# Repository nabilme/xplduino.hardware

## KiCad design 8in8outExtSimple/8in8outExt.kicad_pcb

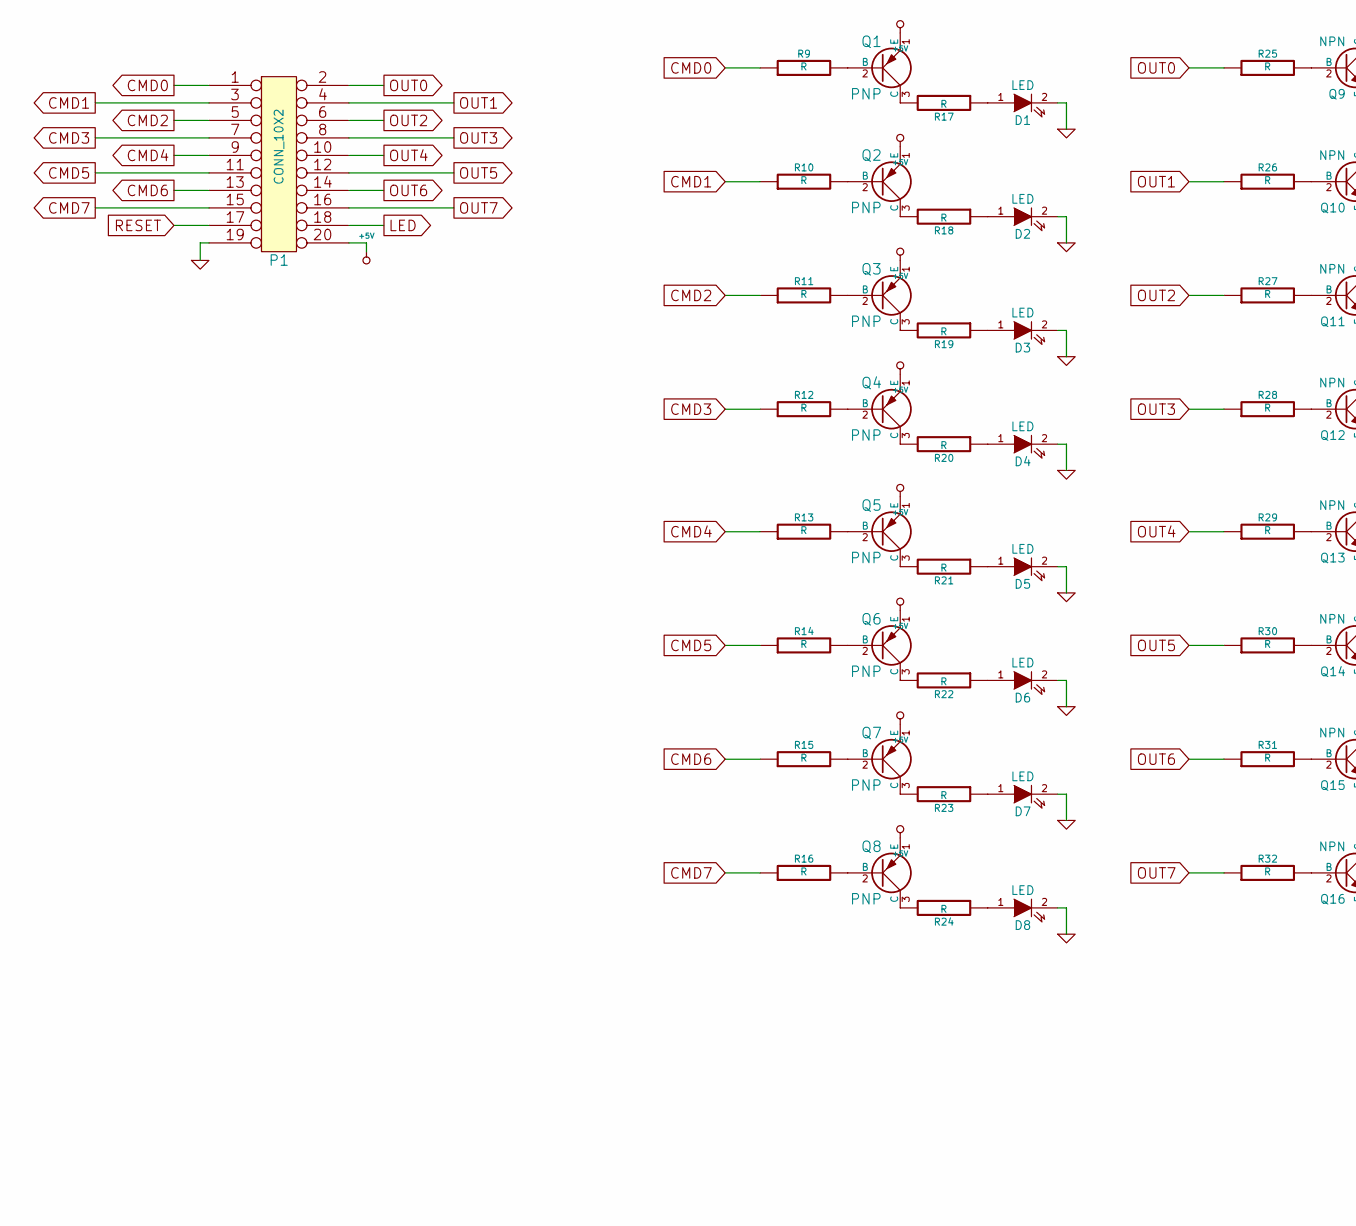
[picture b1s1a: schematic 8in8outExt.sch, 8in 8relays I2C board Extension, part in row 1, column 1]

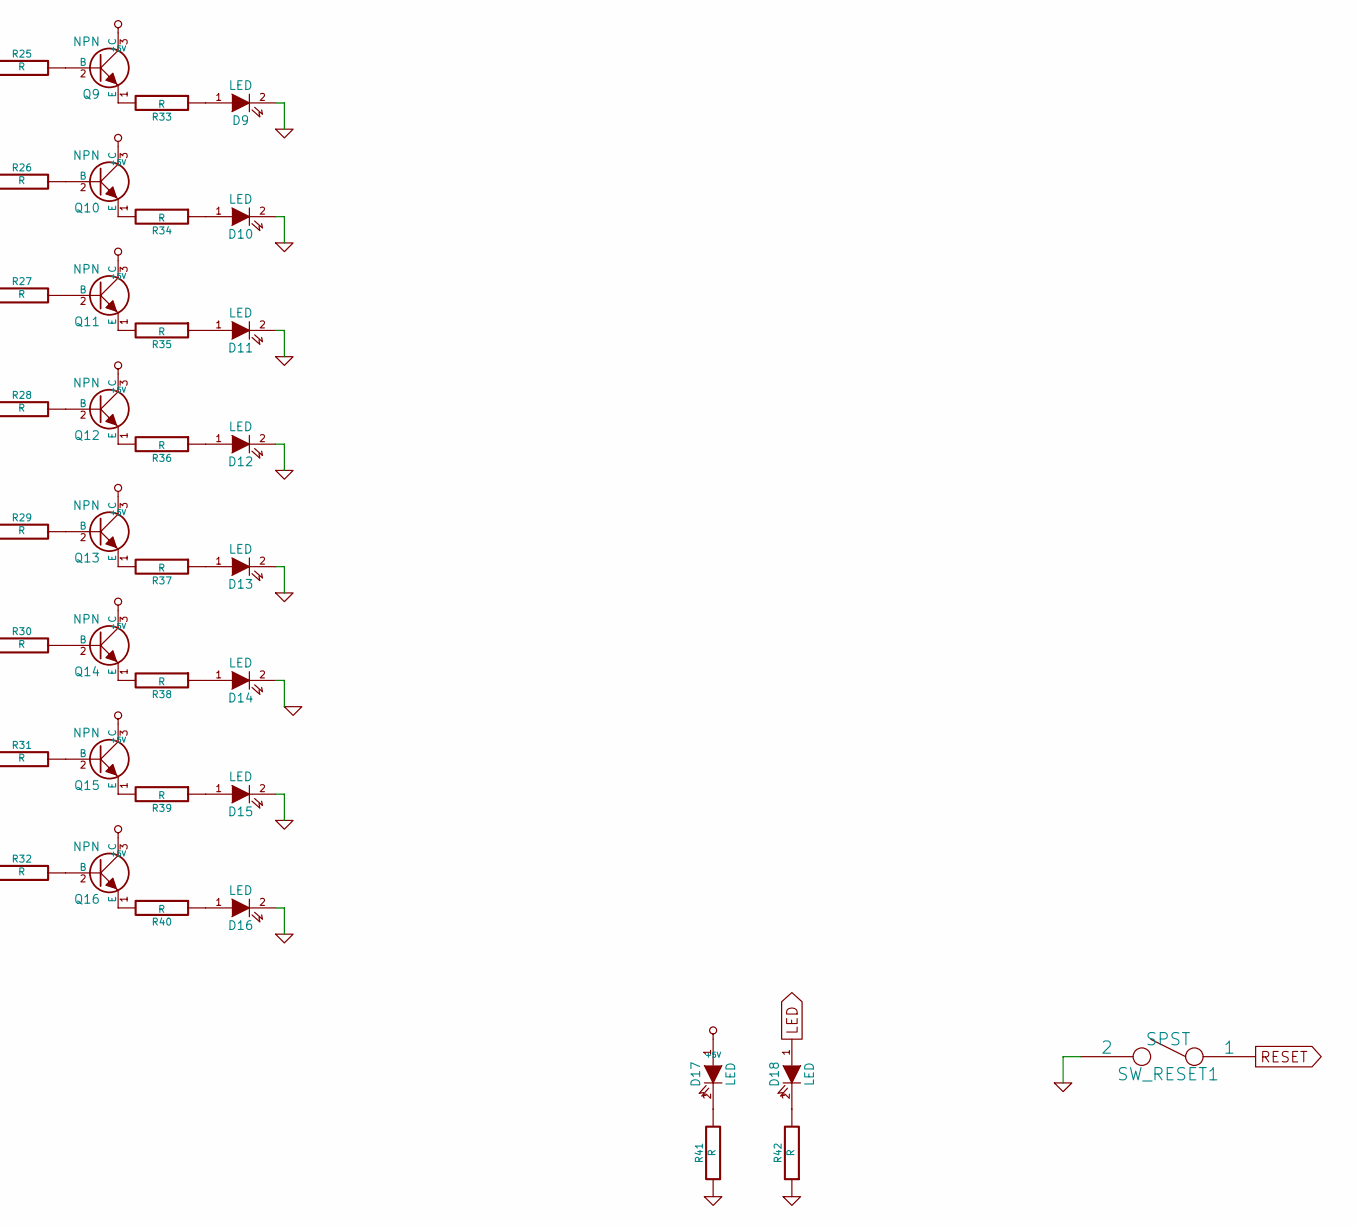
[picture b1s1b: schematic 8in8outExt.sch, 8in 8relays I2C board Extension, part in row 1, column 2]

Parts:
D1, D2, D3, D4, D5, D6, D7, D8, D9, D10, D11, D12, D13, D14, D15, D16, D17, D18: LED
P1: CONN_10X2
Q1, Q2, Q3, Q4, Q5, Q6, Q7, Q8: PNP
Q9, Q10, Q11, Q12, Q13, Q14, Q15, Q16: NPN
R9, R10, R11, R12, R13, R14, R15, R16, R25, R26, R27, R28, R29, R30, R31, R32: R
R17, R18, R19, R20, R21, R22, R23, R24, R33, R34, R35, R36, R37, R38, R39, R40, R41, R42: R
SW_RESET1: SPST

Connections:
+5V: D17.1 (A), P1.20, Q1.1 (E), Q2.1 (E), Q3.1 (E), Q4.1 (E), Q5.1 (E), Q6.1 (E), Q7.1 (E), Q8.1 (E), Q9.3 (C), Q10.3 (C), Q11.3 (C), Q12.3 (C), Q13.3 (C), Q14.3 (C), Q15.3 (C), Q16.3 (C); also elsewhere on the board
CMD0: P1.1, R9.1
CMD1: P1.3, R10.1
CMD2: P1.5, R11.1
CMD3: P1.7, R12.1
CMD4: P1.9, R13.1
CMD5: P1.11, R14.1
CMD6: P1.13, R15.1
CMD7: P1.15, R16.1
unnamed: Q9.2 (B), R25.2
unnamed: Q10.1 (E), R34.2
unnamed: D10.1 (A), R34.1
unnamed: Q9.1 (E), R33.2
unnamed: D9.1 (A), R33.1
unnamed: D11.1 (A), R35.1
unnamed: Q11.2 (B), R27.2
unnamed: Q11.1 (E), R35.2
unnamed: Q10.2 (B), R26.2
unnamed: Q7.3 (C), R23.2
unnamed: D7.1 (A), R23.1
unnamed: Q6.2 (B), R14.2
unnamed: Q6.3 (C), R22.2
unnamed: D6.1 (A), R22.1
unnamed: D8.1 (A), R24.1
unnamed: Q8.2 (B), R16.2
unnamed: Q8.3 (C), R24.2
unnamed: Q7.2 (B), R15.2
unnamed: D16.1 (A), R40.1
unnamed: Q15.2 (B), R31.2
unnamed: Q15.1 (E), R39.2
unnamed: D15.1 (A), R39.1
unnamed: Q14.2 (B), R30.2
unnamed: Q14.1 (E), R38.2
unnamed: Q16.1 (E), R40.2
unnamed: Q16.2 (B), R32.2
unnamed: D13.1 (A), R37.1
unnamed: Q12.2 (B), R28.2
unnamed: Q12.1 (E), R36.2
unnamed: Q13.1 (E), R37.2
unnamed: D12.1 (A), R36.1
unnamed: D14.1 (A), R38.1
unnamed: Q13.2 (B), R29.2
unnamed: D17.2 (K), R41.2
unnamed: Q1.3 (C), R17.2
unnamed: D1.1 (A), R17.1
unnamed: Q4.3 (C), R20.2
unnamed: D4.1 (A), R20.1
unnamed: Q4.2 (B), R12.2
unnamed: Q3.2 (B), R11.2
unnamed: Q3.3 (C), R19.2
unnamed: Q5.2 (B), R13.2
unnamed: Q5.3 (C), R21.2
unnamed: D3.1 (A), R19.1
unnamed: D5.1 (A), R21.1
unnamed: Q1.2 (B), R9.2
unnamed: Q2.2 (B), R10.2
unnamed: Q2.3 (C), R18.2
unnamed: D2.1 (A), R18.1
OUT0: P1.2, R25.1
OUT1: P1.4, R26.1
OUT2: P1.6, R27.1
OUT3: P1.8, R28.1
OUT4: P1.10, R29.1
OUT5: P1.12, R30.1
OUT6: P1.14, R31.1
OUT7: P1.16, R32.1
RESET: P1.17, SW_RESET1.1

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
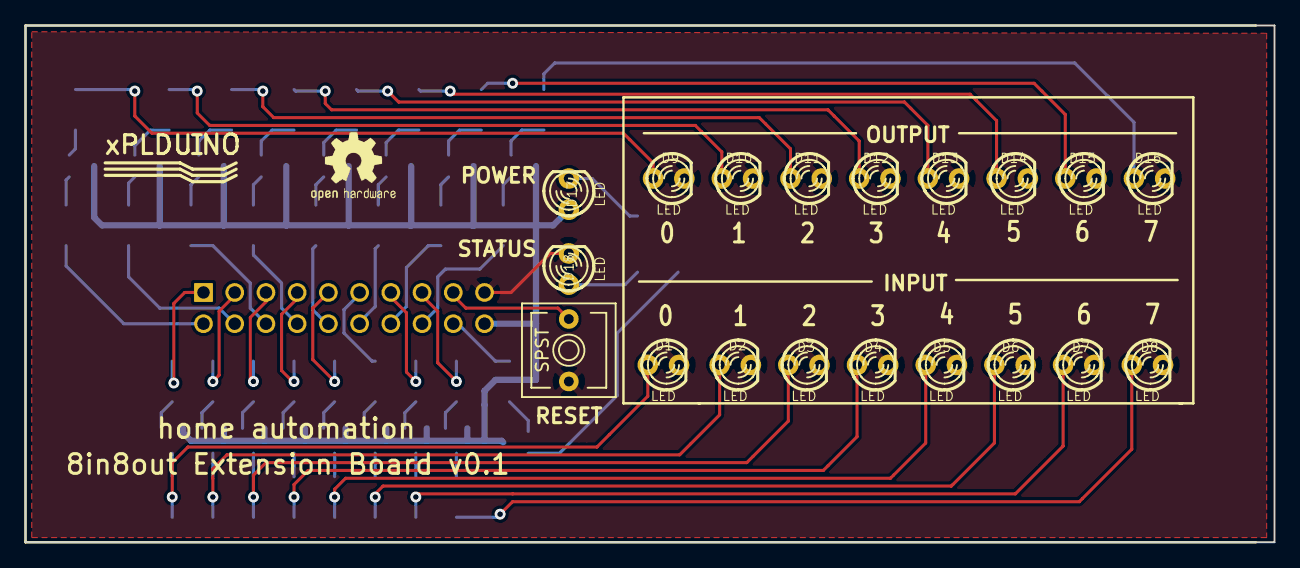
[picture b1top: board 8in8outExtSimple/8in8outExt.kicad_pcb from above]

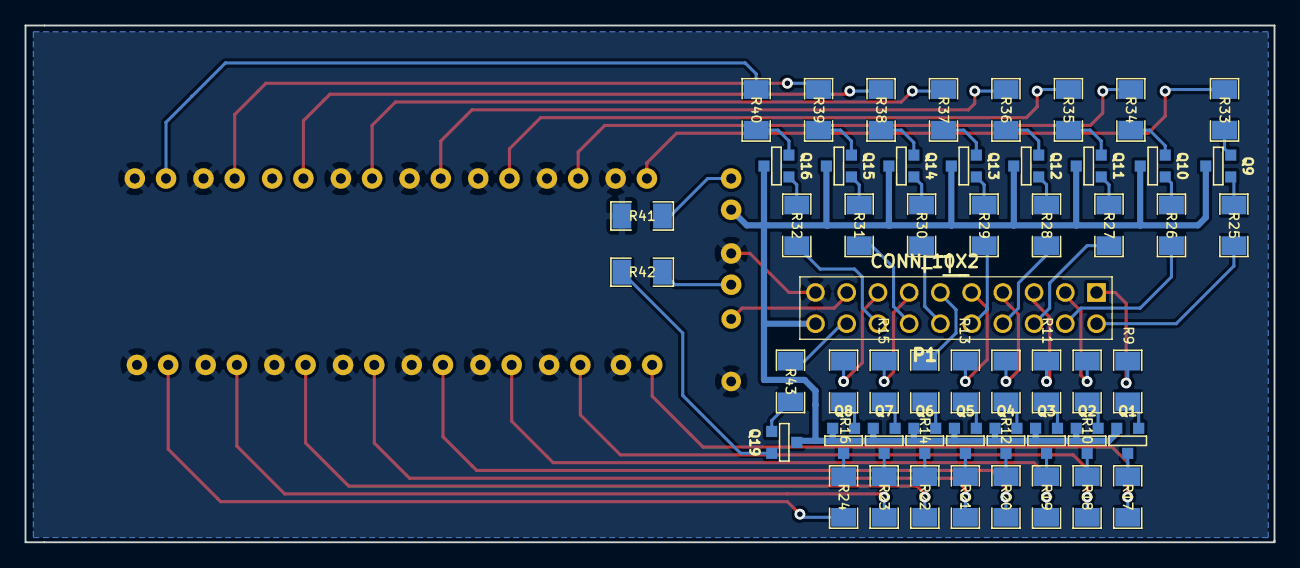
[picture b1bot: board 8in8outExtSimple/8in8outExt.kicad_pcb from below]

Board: 2 copper layers, 101.6 x 42.0 mm, 73 parts (53 on the bottom side), 72 nets.

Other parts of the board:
Q19: NPN; SOT23EBC
R43: R; SM1206
logo_xplduino: VAL**; logo_xplduino

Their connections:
+5V: Q19.3; also elsewhere on the board
unnamed: Q19.2, R43.2

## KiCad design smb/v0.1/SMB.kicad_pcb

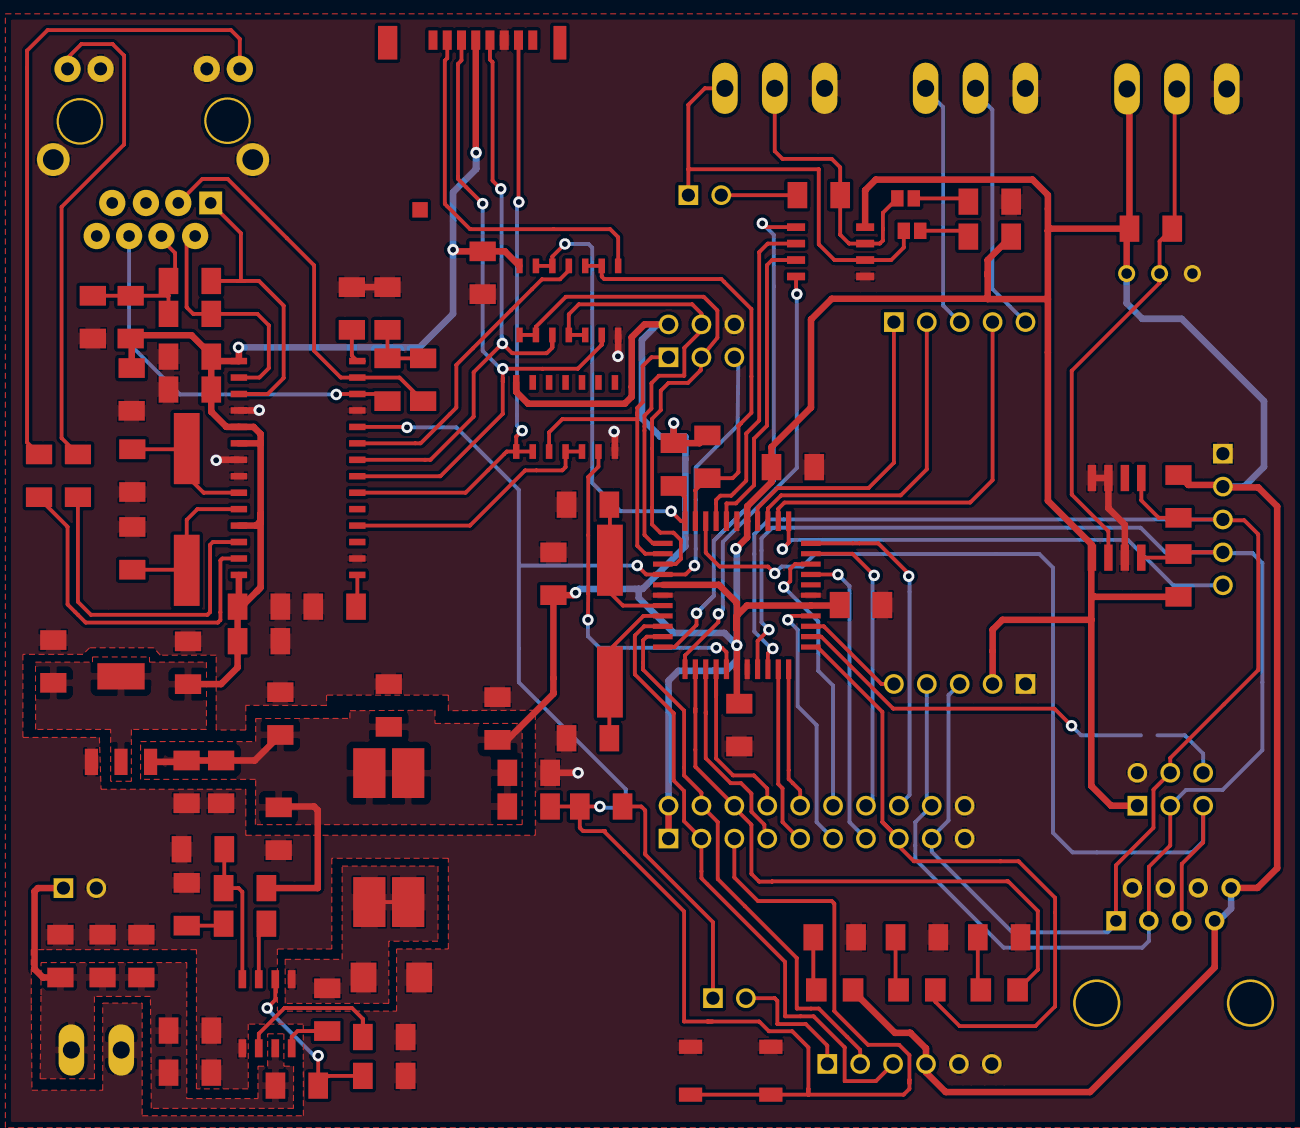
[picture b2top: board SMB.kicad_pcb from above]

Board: 2 copper layers, 98 parts (0 on the bottom side), 80 nets.

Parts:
C101, C102, C103, C104, C107, C203, C204, C205, C206, C207, C215: 0.1uF; SM1206
C105, C106, C201, C202: 18pF; SM1206
C208, C213: 10uF; SM1206POL
C209, C210, C212, C214, C309: 100nF; SM1206
C211: 10nF; SM1206
C301, C303, C304, C310, C311: 1uF; SM1206
C302: 150pF; SM1206POL
C305, C306, C307, C308, C312: 4.7uF; SM1206
D101, D102, D103: LED; LED-1206
D301: B280-13-F; B290-13-F
GS1, GS2, GS3: GS2
IC1: MAX485; SO8E
IC2: DS2482-100S; 1wire-SO08
IC101: ATMEGA1284-A; TQFP44
J101: RJ45; RJ45_BASIC
J102: RTS_RESET; PIN_ARRAY_2X1
J103: ICSP; pin_array_3x2
J104: SERIAL_REV; PIN_ARRAY-6X1
J202: USD_CONN; DM3CS-SF
J401: HR911105_RJ45
L201: 4.7uH; SM1206
L301: SRF1260-150M
P1: CONN_2; PIN_ARRAY_2X1
P2: CONN_3; 1wire-TO92-
P101: I2C_CONN; HE10-6
P102: CONN_10X2; pin_array_10x2
P103, P105, P108: CONN_5; PIN_ARRAY_5x1
P107, P110, P112: CONN_3; MOL_CONN_3_MINI
P109: CONN_3; PIN_ARRAY_2X1
P301: CONN_2; MOL_CONN_2_MINI
R1, R5, R102: 3.3kR; SM1206
R2, R3, R4, R105, R106: R; SM1206
R101, R103, R104: 10k; SM1206
R200: 4.7k; SM1206
R201: 2k32; SM1206
R203, R204, R205, R206: 50; SM1206
R301: 17.4k; SM1206
R302: 100k; SM1206
R303: 200k; SM1206
R304: 158k; SM1206
R305: 40.2k; SM1206
R306: 210k; SM1206
R401, R402: 270R; SM1206
SW101: SKQGAKE010
U201: ENC28J60; SO28
U202: LM1117IMP-3.3; SOT223
U301, U303: 74HC08; SO14E
U302: MP2562DS; SO8E
X101: 20MHz; Q_49U3HMS
X201: 25MHz; Q_49U3HMS
logo_xplduino: VAL**; logo_xplduino

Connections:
3.3V: C203.2, C204.2, C205.1, C206.1, C207.1, C213.1, C214.1, C215.2, J202.4, L201.1, U201.15, U201.19, U201.20, U201.25, U201.28, U202.2, U202.4, U303.14
+5V: C101.1, C102.1, C103.1, C104.2, C211.1, C212.1, C305.1, C306.1, C307.1, C308.1, C312.1, D102.1, IC1.8, IC2.1, IC101.5, IC101.17, IC101.27, IC101.38, J101.7, J101.8, J103.2, J104.4, L301.3, L301.4, P2.3, P101.1, P102.1, P102.2, P105.2, P108.2, P110.3, R3.2, R101.1, R103.1, R104.1, R105.1, R106.1, R200.1, R306.2, U202.3, U301.14
+12V: C301.1, C303.1, C304.1, C310.1, C311.1, P1.1, P301.1, R302.1, U302.7
/INT_I2C: IC101.42, J101.5, P101.5
/RESET: C107.2, IC101.4, J103.5, P102.5, R104.2, SW101.1, SW101.2, U201.10
/SPARE: GS1.1, P101.6
CLK_33: J202.5, U201.8, U303.3
CS_33: J202.2, U303.8
ETH_CS: IC101.44, R101.2, U303.12, U303.13
ETH_CS_33: U201.9, U303.11
ETH_INT: IC101.16, U301.6
GND: C101.2, C102.2, C103.2, C104.1, C105.2, C106.2, C201.2, C202.2, C203.1, C204.1, C205.2, C206.2, C207.2, C208.2, C209.2, C210.2, C211.2, C212.2, C213.2, C214.2, C215.1, C301.2, C303.2, C304.2, C305.2, C306.2, C307.2, C308.2, C310.2, C311.2, C312.2, D301.1, IC1.5, IC2.3, IC2.7, IC2.8, IC101.6, IC101.18, IC101.28, IC101.39, J101.2, J101.4, J101.6, J103.6, J104.5, J104.6, J202.6, J401.0, J401.10, J401.11, P1.2, P2.1, P101.2, P102.19, P102.20, P105.1, P107.1, P108.1, P110.1, P112.1, P301.2, R1.2, R4.2, R5.2, R102.2, R201.2, R301.2, R303.2, R304.2, R305.2, SW101.3, SW101.4, U201.2, U201.11, U201.18, U201.21, U201.22, U202.1, U301.7, U302.5, U303.7
LED_FAULT: D103.1, IC101.23, P102.15
LED_STATUS: D101.1, IC101.13, P102.6
MISO_33: J202.7, U201.6, U301.1, U301.2
MOSI_33: J202.3, U201.7, U303.6
unnamed: C105.1, IC101.7, X101.1
unnamed: C106.1, IC101.8, X101.2
unnamed: J102.2, J104.1
unnamed: C107.1, J102.1
unnamed: GS3.2, R4.1
unnamed: P109.2, R2.2
unnamed: GS2.2, R3.1
unnamed: IC2.2, P2.2, P110.2, R200.2
unnamed: P103.3, P112.3
unnamed: P103.5, P112.2
unnamed: D103.2, R5.1
unnamed: GS1.2, IC101.24
unnamed: D101.2, R102.1
unnamed: D102.2, R1.1
unnamed: J401.6, R206.1, U201.12
unnamed: C208.1, U201.1
unnamed: R402.1, U201.26
unnamed: J401.12, R402.2
unnamed: C210.1, J401.4, L201.2, R203.1, R204.1
unnamed: J401.1, R204.2, U201.17
unnamed: J401.3, R205.1, U201.13
unnamed: C209.1, R205.2, R206.2
unnamed: R401.1, U201.27
unnamed: J401.9, R401.2
unnamed: J401.2, R203.2, U201.16
unnamed: U201.4, U301.4, U301.5
unnamed: R201.1, U201.14
unnamed: C202.1, U201.24, X201.2
unnamed: C201.1, U201.23, X201.1
unnamed: C302.2, R304.1
unnamed: R301.1, R302.2, U302.2
unnamed: R303.1, U302.6
unnamed: C302.1, U302.3
unnamed: C309.1, U302.8
unnamed: R305.1, R306.1, U302.4
PA0: IC101.37, P103.1
PA1: IC101.36, P103.2
PA2: IC101.35, P103.4
PA3: IC101.34, P105.5
PA4: IC101.33, P102.16
PA5: IC101.32, P102.14
PA6: IC101.31, P102.12
PA7: IC101.30, P102.13
PB0: IC1.3, IC101.40
PB1: IC1.2, IC101.41
PC2: IC101.21, P102.9
PC3: IC101.22, P102.10
PC6: IC101.25, P108.5
PC7: IC101.26, P102.11
PD5: IC101.14, P102.7
PD6: IC101.15, P102.8
RX0: IC101.9, J104.3, P102.3
RX1: IC1.1, IC101.11
SCL: IC2.4, IC101.19, J101.3, P101.3, P102.18, P105.4, P108.4, R106.2
SDA: IC2.5, IC101.20, J101.1, P101.4, P102.17, P105.3, P108.3, R105.2
SPI_CLK: IC101.3, J103.3, U303.1, U303.2
SPI_MISO: IC101.2, J103.1, U301.3
SPI_MOSI: IC101.1, J103.4, U303.4, U303.5
TX0: IC101.10, J104.2, P102.4
TX1: IC1.4, IC101.12
TX+: GS2.1, IC1.6, P107.3, P109.1
TX-: GS3.1, IC1.7, P107.2, R2.1
pre_5V: C309.2, D301.2, L301.1, L301.2, U302.1
uSD_CS: IC101.43, R103.2, U303.9, U303.10

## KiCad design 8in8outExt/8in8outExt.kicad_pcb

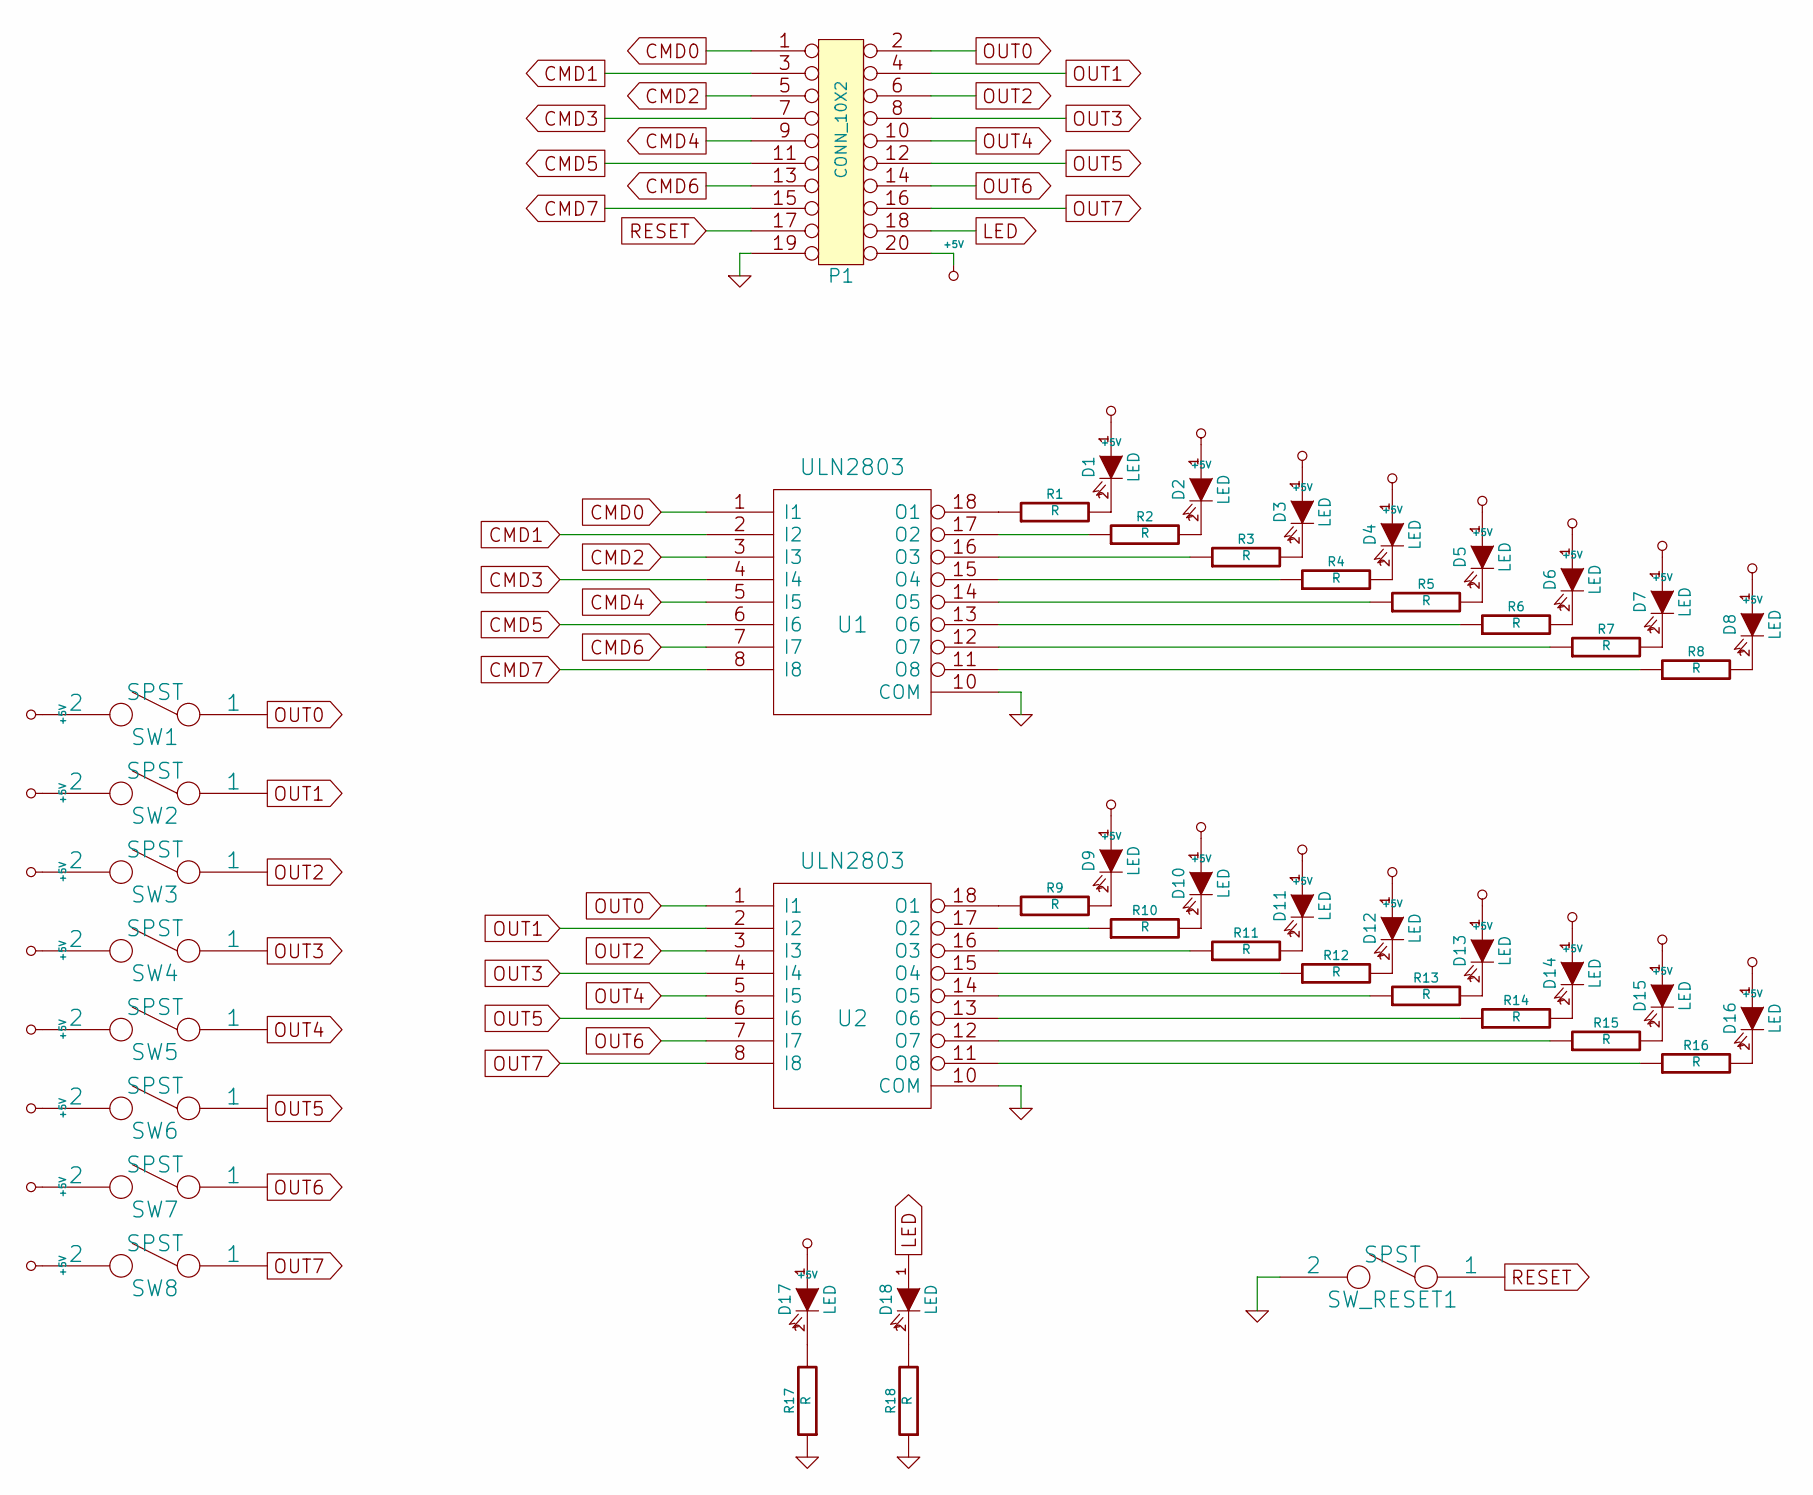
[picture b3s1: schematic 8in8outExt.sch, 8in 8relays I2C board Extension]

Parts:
D1, D2, D3, D4, D5, D6, D7, D8, D9, D10, D11, D12, D13, D14, D15, D16, D17, D18: LED
P1: CONN_10X2
R1, R2, R3, R4, R5, R6, R7, R8, R9, R10, R11, R12, R13, R14, R15, R16, R17, R18: R
SW1, SW2, SW3, SW4, SW5, SW6, SW7, SW8: SPST
SW_RESET1: SPST
U1, U2: ULN2803

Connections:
+5V: D1.1 (A), D2.1 (A), D3.1 (A), D4.1 (A), D5.1 (A), D6.1 (A), D7.1 (A), D8.1 (A), D9.1 (A), D10.1 (A), D11.1 (A), D12.1 (A), D13.1 (A), D14.1 (A), D15.1 (A), D16.1 (A), D17.1 (A), P1.20, SW1.2, SW2.2, SW3.2, SW4.2, SW5.2, SW6.2, SW7.2, SW8.2
CMD0: P1.1, U1.1 (I1)
CMD1: P1.3, U1.2 (I2)
CMD2: P1.5, U1.3 (I3)
CMD3: P1.7, U1.4 (I4)
CMD4: P1.9, U1.5 (I5)
CMD5: P1.11, U1.6 (I6)
CMD6: P1.13, U1.7 (I7)
CMD7: P1.15, U1.8 (I8)
GND: P1.19, R17.1, R18.1, SW_RESET1.2, U1.9 (GND), U1.10 (COM), U2.9 (GND), U2.10 (COM)
LED: D18.1 (A), P1.18
unnamed: D16.2 (K), R16.2
unnamed: R16.1, U2.11 (O8)
unnamed: D15.2 (K), R15.2
unnamed: R15.1, U2.12 (O7)
unnamed: D13.2 (K), R13.2
unnamed: R13.1, U2.14 (O5)
unnamed: D11.2 (K), R11.2
unnamed: R11.1, U2.16 (O3)
unnamed: D9.2 (K), R9.2
unnamed: R9.1, U2.18 (O1)
unnamed: D14.2 (K), R14.2
unnamed: D12.2 (K), R12.2
unnamed: R14.1, U2.13 (O6)
unnamed: R12.1, U2.15 (O4)
unnamed: R10.1, U2.17 (O2)
unnamed: D10.2 (K), R10.2
unnamed: D18.2 (K), R18.2
unnamed: D17.2 (K), R17.2
unnamed: R5.1, U1.14 (O5)
unnamed: R6.1, U1.13 (O6)
unnamed: R7.1, U1.12 (O7)
unnamed: R8.1, U1.11 (O8)
unnamed: R4.1, U1.15 (O4)
unnamed: D4.2 (K), R4.2
unnamed: R3.1, U1.16 (O3)
unnamed: R2.1, U1.17 (O2)
unnamed: D2.2 (K), R2.2
unnamed: D6.2 (K), R6.2
unnamed: D8.2 (K), R8.2
unnamed: D7.2 (K), R7.2
unnamed: D5.2 (K), R5.2
unnamed: D3.2 (K), R3.2
unnamed: R1.1, U1.18 (O1)
unnamed: D1.2 (K), R1.2
OUT0: P1.2, SW1.1, U2.1 (I1)
OUT1: P1.4, SW2.1, U2.2 (I2)
OUT2: P1.6, SW3.1, U2.3 (I3)
OUT3: P1.8, SW4.1, U2.4 (I4)
OUT4: P1.10, SW5.1, U2.5 (I5)
OUT5: P1.12, SW6.1, U2.6 (I6)
OUT6: P1.14, SW7.1, U2.7 (I7)
OUT7: P1.16, SW8.1, U2.8 (I8)
RESET: P1.17, SW_RESET1.1

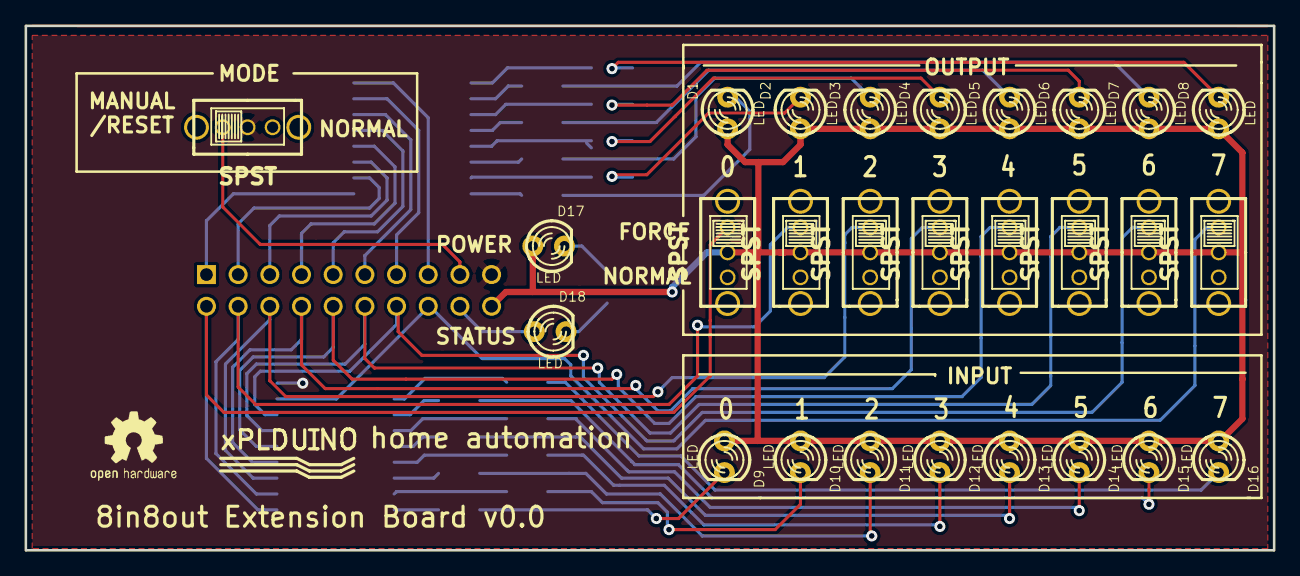
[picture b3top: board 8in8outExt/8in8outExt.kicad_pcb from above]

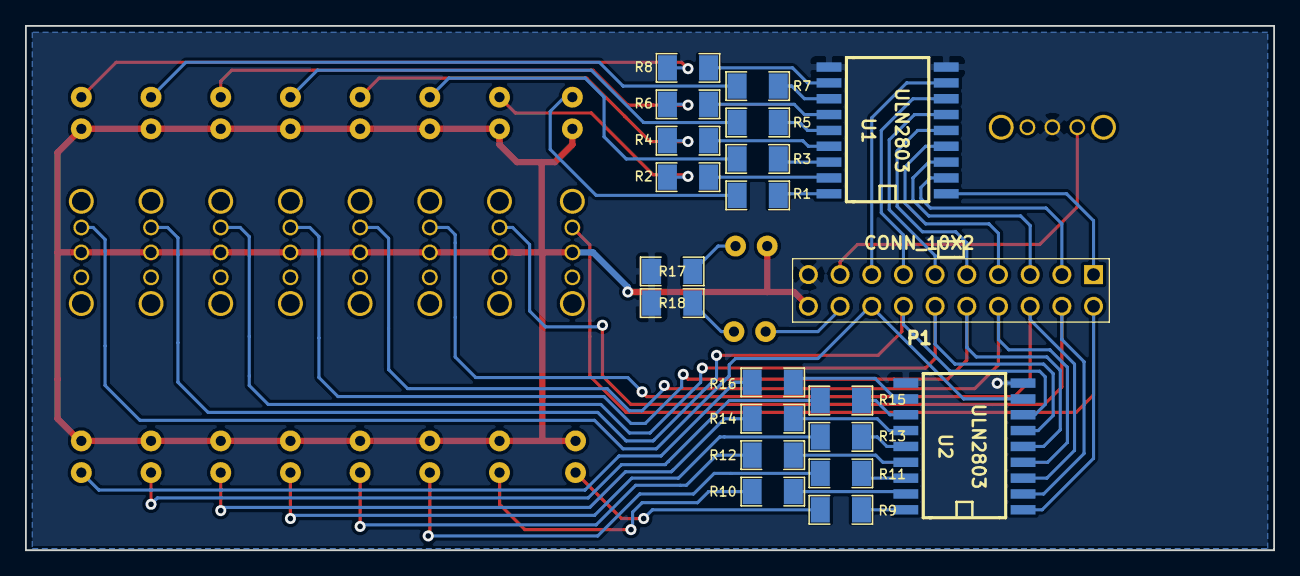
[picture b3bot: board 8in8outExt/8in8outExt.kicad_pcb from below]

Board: 2 copper layers, 100.1 x 42.0 mm, 49 parts (21 on the bottom side), 54 nets.

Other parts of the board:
logo_xplduino: VAL**; logo_xplduino

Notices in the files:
8in8out/8in8out.kicad_pcb:
GNU GPL v2
